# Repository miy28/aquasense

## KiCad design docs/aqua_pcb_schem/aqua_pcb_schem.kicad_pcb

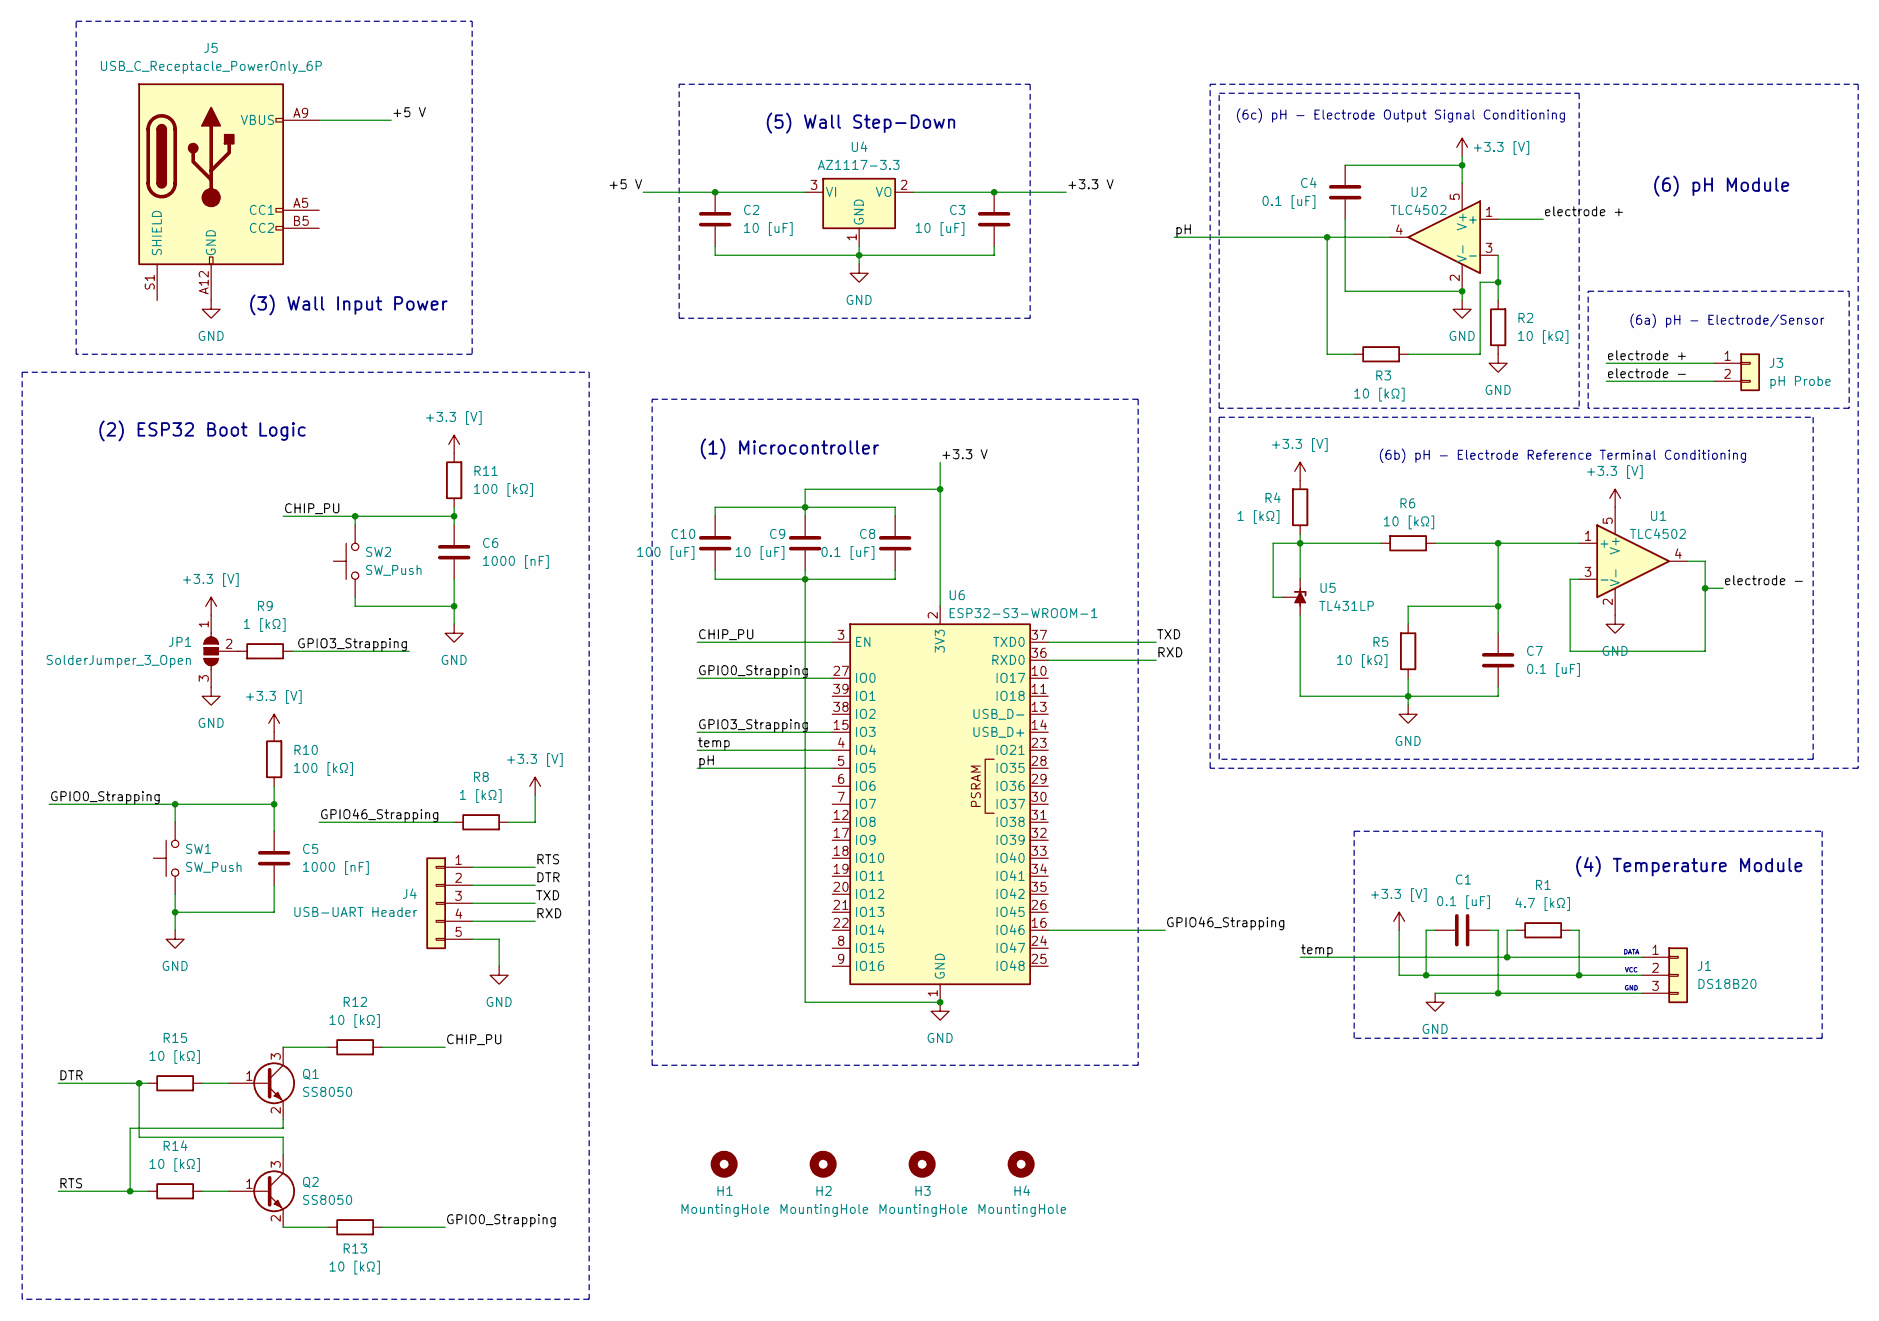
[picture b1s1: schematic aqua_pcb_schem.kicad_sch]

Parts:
C1, C4, C7, C8: 0.1 [uF]; C_0805_2012Metric_Pad1.18x1.45mm_HandSolder
C2, C3, C9: 10 [uF]; C_0805_2012Metric_Pad1.18x1.45mm_HandSolder
C5, C6: 1000 [nF]; C_0805_2012Metric_Pad1.18x1.45mm_HandSolder
C10: 100 [uF]; C_0805_2012Metric_Pad1.18x1.45mm_HandSolder
H1, H2, H3, H4: MountingHole; MountingHole_3.2mm_M3
J1: DS18B20; TerminalBlock_Phoenix_PT-1,5-2-3.5-H_1x02_P3.50mm_Horizontal
J3: pH Probe; BNC_Amphenol_031-6575_Horizontal
J4: USB-UART Header; QFN-64-1EP_9x9mm_P0.5mm_EP4.1x4.1mm
J5: USB_C_Receptacle_PowerOnly_6P; USB_C_Receptacle_Amphenol_124019772112A
JP1: SolderJumper_3_Open; SolderJumper-3_P1.3mm_Open_Pad1.0x1.5mm
Q1, Q2: SS8050; SOT-23
R1: 4.7 [kΩ]; R_0805_2012Metric_Pad1.20x1.40mm_HandSolder
R2, R3, R5, R6, R12, R13, R14, R15: 10 [kΩ]; R_0805_2012Metric_Pad1.20x1.40mm_HandSolder
R4, R8, R9: 1 [kΩ]; R_0805_2012Metric_Pad1.20x1.40mm_HandSolder
R10, R11: 100 [kΩ]; R_0805_2012Metric_Pad1.20x1.40mm_HandSolder
SW1, SW2: SW_Push; SW_PUSH_1P1T_6x3.5mm_H5.0_APEM_MJTP1250
U1, U2: TLC4502; SOT-353_SC-70-5
U4: AZ1117-3.3; SOT-223
U5: TL431LP; TO-92_Inline
U6: ESP32-S3-WROOM-1

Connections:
+3.3 [V]: C1.1, C4.1, J1.2, JP1.1 (A), R1.2, R4.2, R8.2, R10.2, R11.2, U1.5 (V+), U2.5 (V+)
/+3.3 V: C3.1, C8.1, C9.1, C10.1, U4.2 (VO), U6.2 (3V3)
/+5 V: C2.1, J5.A9 (VBUS), J5.B9 (VBUS), U4.3 (VI)
/CHIP_PU: C6.1, R11.1, R12.2, SW2.2, U6.3 (EN)
/DTR: J4.2, Q2.3 (C), R15.1
/GPIO0_Strapping: C5.1, R10.1, R13.2, SW1.2, U6.27 (IO0)
/GPIO3_Strapping: R9.1, U6.15 (IO3)
/GPIO46_Strapping: R8.1, U6.16 (IO46)
/RTS: J4.1, Q1.2 (E), R14.1
/RXD: J4.4, U6.36 (RXD0)
/TXD: J4.3, U6.37 (TXD0)
/electrode +: J3.1, U2.1 (+)
/electrode -: J3.2, U1.3 (-), U1.4
/pH: R3.1, U2.4, U6.5 (IO5)
/temp: J1.1, R1.1, U6.4 (IO4)
GND: C1.2, C2.2, C3.2, C4.2, C5.2, C6.2, C7.2, C8.2, C9.2, C10.2, J1.3, J4.5, J5.A12 (GND), J5.B12 (GND), JP1.3 (B), R2.1, R5.1, SW1.1, SW2.1, U1.2 (V-), U2.2 (V-), U4.1 (GND), U5.2 (A), U6.1 (GND), U6.40 (GND), U6.41 (GND)
unnamed: JP1.2 (C), R9.2
unnamed: Q1.1 (B), R15.2
unnamed: Q1.3 (C), R12.1
unnamed: Q2.1 (B), R14.2
unnamed: Q2.2 (E), R13.1
unnamed: C7.1, R5.2, R6.1, U1.1 (+)
unnamed: R2.2, R3.2, U2.3 (-)
unnamed: R4.1, R6.2, U5.1 (REF), U5.3 (K)

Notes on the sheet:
(3) Wall Input Power
(6a) pH - Electrode/Sensor
(2) ESP32 Boot Logic
(6c) pH - Electrode Output Signal Conditioning
(5) Wall Step-Down
VCC
(1) Microcontroller
DATA
(6b) pH - Electrode Reference Terminal Conditioning
GND
(4) Temperature Module
(6) pH Module

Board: 2 copper layers, 42 parts (0 on the bottom side), 24 nets, no tracks yet.

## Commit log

2025-03-09 set up basic server and backend to support the esp32 demo
2025-03-09 added datetime + visualization
2025-03-10 a commit
2025-03-11 almost done for demo
2025-03-26 finalized pcb schematic
2025-03-26 basic frontend + llm setup
2025-03-28 for meeting
2025-04-01 schematic and parts all finalized. gotta order today
2025-04-07 adding updated gerber zip
2025-04-14 digikey parts finalized
2025-04-14 added front end dash to master
2025-04-17 front end updates + ml threshold detection and response
2025-04-22 frontend rework + rebase from anu-dev
2025-04-24 Adding Principal Component Analysis for Temperature Data Anomaly Detection (Threshold as 3.0)
2025-04-24 Frontend Update: Current Time, LLM Display, Brightness Data Display
2025-04-24 GPT 2 LLM Server Drop + (Backend/Frontend Updates)
2025-04-24 functional changes anu
2025-04-26 workiing code 4-26 pre pH
2025-04-26 light update
2025-04-26 its over (backend at least)
2025-04-29 its all over
2025-04-29 its over
2025-04-29 pickle
2025-05-09 added michael's notebook
2025-05-09 lab notebook added anurag
